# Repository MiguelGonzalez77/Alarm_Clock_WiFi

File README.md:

# Alarm_Clock_WiFi
Create and extend an alarm clock by adding WiFi communication and an HTML client that could remotely access the device. This involved designing and implementing a “smart object” by using a MQTT Broker to subscribe/publish messages from the TM4C ucontroller to the web page and back.

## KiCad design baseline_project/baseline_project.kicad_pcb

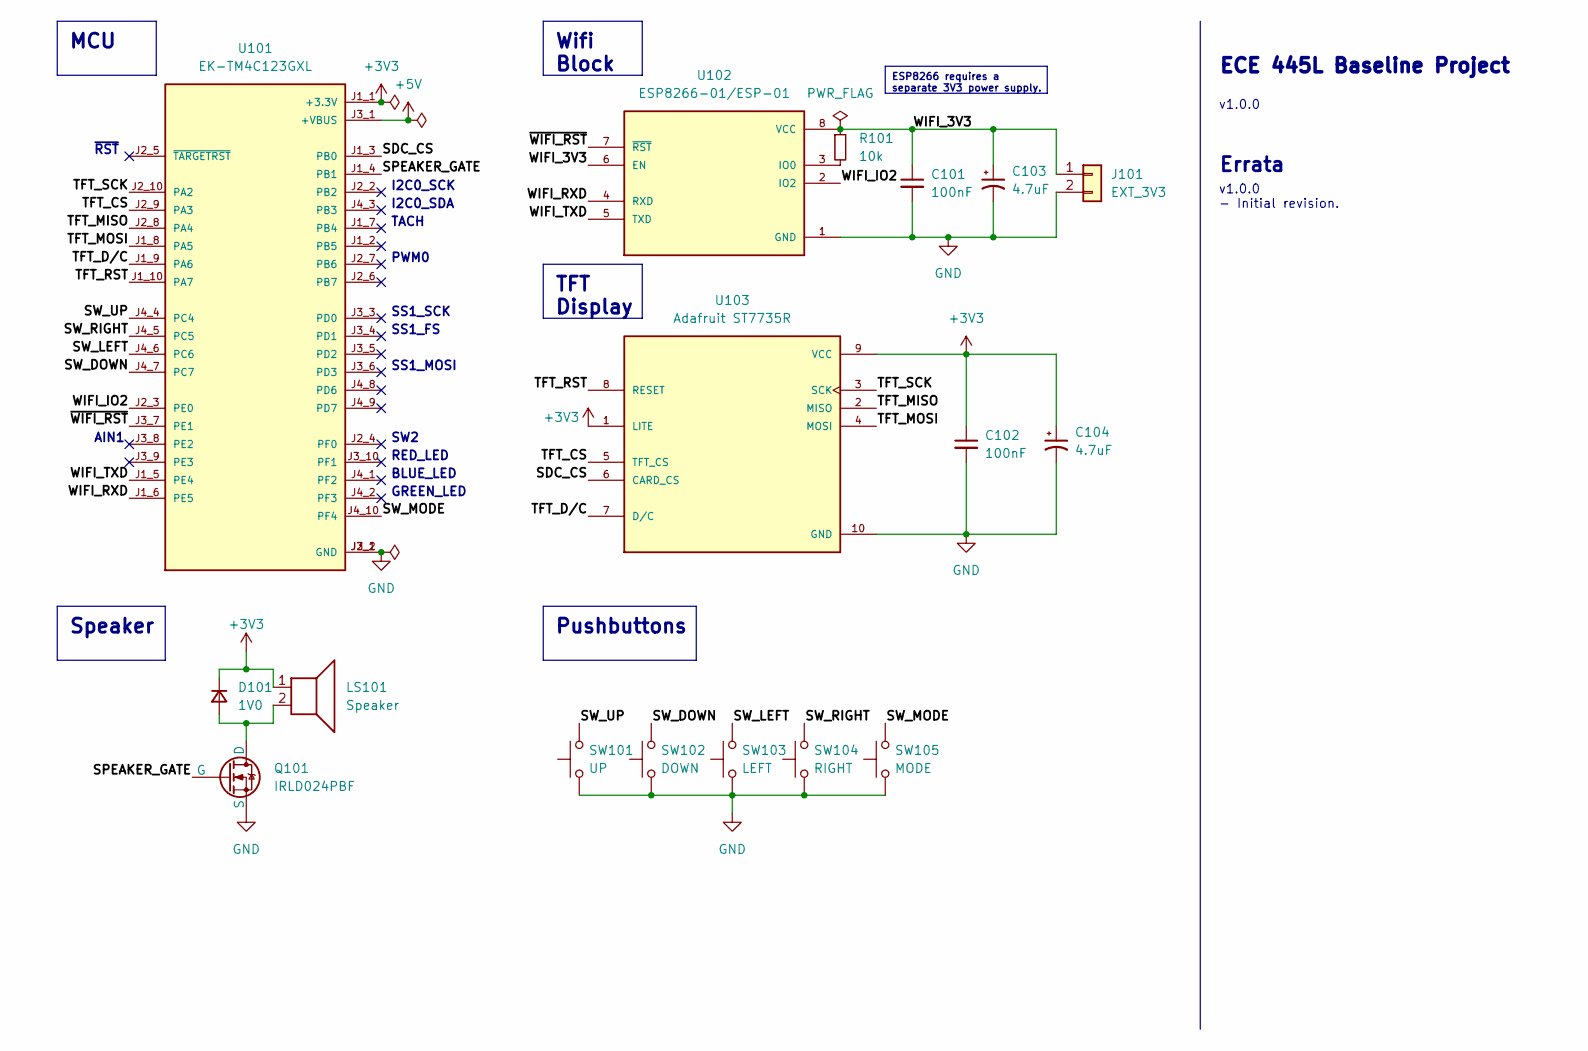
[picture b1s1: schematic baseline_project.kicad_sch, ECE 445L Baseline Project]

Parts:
C101, C102: 100nF; C_Axial_L5.1mm_D3.1mm_P15.00mm_Horizontal
C103, C104: 4.7uF; CP_Axial_L10.0mm_D4.5mm_P15.00mm_Horizontal
D101: 1V0; D_5W_P12.70mm_Horizontal
J101: EXT_3V3; Samtec_HPM-02-01-x-S_Straight_1x02_Pitch5.08mm
LS101: Speaker; PinHeader_1x02_P2.54mm_Vertical
Q101: IRLD024PBF; vishay_IRLD024PBF
R101: 10k; R_Axial_DIN0411_L9.9mm_D3.6mm_P15.24mm_Horizontal
SW101: UP; SW_PUSH_6mm
SW102: DOWN; SW_PUSH_6mm
SW103: LEFT; SW_PUSH_6mm
SW104: RIGHT; SW_PUSH_6mm
SW105: MODE; SW_PUSH_6mm
U101: EK-TM4C123GXL; ti_EKTM4C123GXL
U102: ESP8266-01/ESP-01; ai_thinker_ESP8266_01
U103: Adafruit ST7735R; adafruit_st7735r

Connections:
+3V3: C102.1, C104.1, D101.1 (K), LS101.1, U101.J1_1 (+3.3V), U103.1 (LITE), U103.9 (VCC)
+5V: U101.J3_1 (+VBUS)
/SDC_CS: U101.J1_3 (PB0), U103.6 (CARD_CS)
/SPEAKER_GATE: Q101.2 (G), U101.J1_4 (PB1)
/SW_DOWN: SW102.2, U101.J4_7 (PC7)
/SW_LEFT: SW103.2, U101.J4_6 (PC6)
/SW_MODE: SW105.2, U101.J4_10 (PF4)
/SW_RIGHT: SW104.2, U101.J4_5 (PC5)
/SW_UP: SW101.2, U101.J4_4 (PC4)
/TFT_CS: U101.J2_9 (PA3), U103.5 (TFT_CS)
/TFT_D/C: U101.J1_9 (PA6), U103.7 (D/C)
/TFT_MISO: U101.J2_8 (PA4), U103.2 (MISO)
/TFT_MOSI: U101.J1_8 (PA5), U103.4 (MOSI)
/TFT_RST: U101.J1_10 (PA7), U103.8 (RESET)
/TFT_SCK: U101.J2_10 (PA2), U103.3 (SCK)
/WIFI_3V3: C101.1, C103.1, J101.1, R101.1, U102.6 (EN), U102.8 (VCC)
/WIFI_IO2: U101.J2_3 (PE0), U102.2 (IO2)
/WIFI_RXD: U101.J1_6 (PE5), U102.4 (RXD)
/WIFI_TXD: U101.J1_5 (PE4), U102.5 (TXD)
/~WIFI_RST: U101.J3_7 (PE1), U102.7 (~RST)
GND: C101.2, C102.2, C103.2, C104.2, J101.2, Q101.3 (S), SW101.1, SW102.1, SW103.1, SW104.1, SW105.1, U101.J2_1 (GND), U101.J3_2 (GND), U102.1 (GND), U103.10 (GND)
unnamed: D101.2 (A), LS101.2, Q101.1 (D)
unnamed: R101.2, U102.3 (IO0)

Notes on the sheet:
MCU
ESP8266 requires a separate 3V3 power supply.
Speaker
Pushbuttons
TFT Display
Wifi Block
SS1_FS
SS1_MOSI
I2C0_SCK
v1.0.0 - Initial revision.
~{RST}
PWM0
TACH
AIN1
ECE 445L Baseline Project
v1.0.0
Errata
BLUE_LED
I2C0_SDA
SS1_SCK
RED_LED
SW2
GREEN_LED

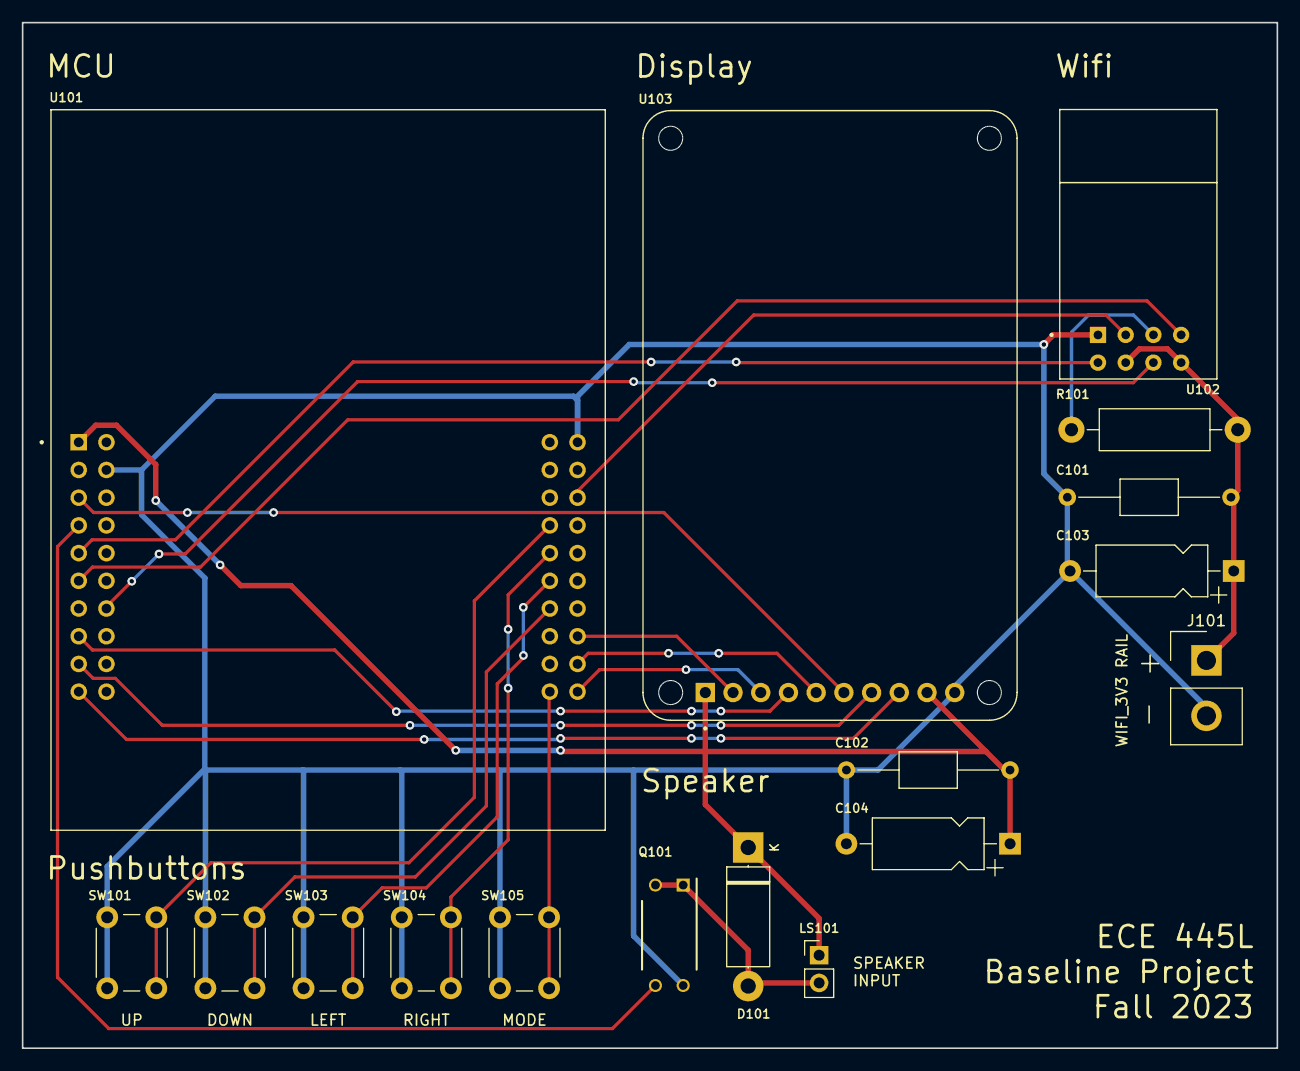
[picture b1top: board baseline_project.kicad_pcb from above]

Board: 2 copper layers, 115.0 x 94.0 mm, 17 parts (0 on the bottom side), 22 nets.

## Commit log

2026-03-20 Placeholder for now of the KiCAD Schematic
2026-03-20 Added filter
2026-03-20 Added starter files/Filters as examples
2026-03-20 Added alarm clock disp to LCD
